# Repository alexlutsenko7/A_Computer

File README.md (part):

# L

**Supported hardware (since 2026-11-23): the QMTECH Cyclone 10 LP core board (10CL025) with I/O board revision 2
and the firmware `ESP32/v2`.** The first set, the Cyclone IV EP4CE15 core board with I/O board revision 1 and the
firmware `ESP32/v1`, is **no longer supported**: its FPGA and the ESP32 module without extra memory are too small
for the newer machines and functions. Everything for it stays in this repository as it was last built and tested
(sources, `ep4_ce15/` projects, `ESP32/v1`, the files in `INSTALL/`), because the book describes it; it gets no
new functions and is not built or tested any more. The `<machine>/ep4_ce15/` folders also hold the sources that the
10CL025 projects use, so they go on changing; a change there is tried on the 10CL025 only.

Retro computers in an FPGA: an Intel/Altera Cyclone IV E (EP4CE15F23C8) on a QMTECH core board, with the RAM and
ROMs in the board's SDRAM, VGA output, a USB keyboard and an ESP32 system controller (SD card loader, on-screen
menus, Bluetooth audio). A machine menu at power-up chooses the machine:

- **LSpectrum**, a ZX Spectrum 128K with a built-in SD card tape loader that plays unmodified `.tap` / `.tzx` files,
  saves programs back to the card, and saves / loads `.z80` snapshots;
- **L64**, a Commodore 64 (PAL) with a 1541 disk drive that reads and writes `.d64` images, `.prg` / `.t64`
  loading, C64 `.tap` tapes, turbo loading and `.a64` snapshots;
- **LTari**, an Atari 800XL (**LTari 800**, 64 KB) or 130XE (**LTari 130**, 128 KB) with its own ANTIC, GTIA, POKEY
  and PIA, an SD card disk drive (`.atr`), `.xex` / `.com` programs, cartridges (`.car`) and `.a8s` snapshots.

Status (October 2026): the menu, LSpectrum, L64 and LTari work on hardware.

**Licences, what is our own work, and the complete build guide (including the C64 ROM files you have to get
yourself): [BUILDING_AND_LICENSES.md](BUILDING_AND_LICENSES.md).**

## Features

- **ZX Spectrum 128K**: T80 Z80 core at the exact 3.5469 MHz, or 28 MHz turbo; 128 KB RAM with 7FFD paging; 128K
  ROM set and DiagROM; AY-3-8912 (JT49); beeper; Kempston joystick; 50 Hz interrupt; memory contention (128K
  timing, memory and I/O cycles; not cycle-exact) and the floating bus, so most timing-critical games and border
  effects run as on the real machine.
- **Memory in SDRAM**: own 112 MHz controller for the W9825G6KH (open-row, CAS latency 2); the CPU is stepped by a
  clock enable and simply waits when the SDRAM is busy. The screen is mirrored in block RAM for the video.
- **Video**: VGA 720x576@50 (576p) or 640x480@60, 2 bits per colour, switchable at run time.
- **USB keyboard** through a CH9350-style UART module, with machine keys: DiagROM, 50/60 Hz, reset.
- **SD card tape loader** on an ESP32 system controller (firmware in C, SPI link to the FPGA):
  - on-screen browser (folders, long names, up to 320 entries), FAT16 / FAT32;
  - plays TAP and TZX (incl. turbo blocks, pure tones, pulse sequences, direct recordings, loops, jumps, calls,
    stop blocks) T-state exact, in turbo (8x) or at normal speed;
  - saves: everything the Spectrum `SAVE`s goes into a `.tap` file on the card;
  - pause, back one block, stop;
  - **snapshots**: F2 saves the whole machine as a `.z80` (version 3, 128K) at any moment; the browser loads
    `.z80` files (versions 1-3, 48K and 128K).
- **Bluetooth audio**: the same ESP32-WROOM-32 (`ESP32/v2/`, Arduino) takes the sound as I2S and sends it to Bluetooth
  speakers / headphones (A2DP), including old PIN-only devices; F3 opens the on-screen Bluetooth menu.
- **L64** (`L64/ep4_ce15/README.md`): VIC-II Kawari, T65 as 6510, the MiSTer SID 6581/8580 and CIAs, our bus, PLA
  and 1541 drive (T65, two VIAs, GCR on the fly from a track buffer the ESP32 fills from the `.d64`). The
  picture goes through a frame buffer in SDRAM: 800x600 at 60 Hz, or the C64's own 50 Hz (F8). Turbo loading (F6):
  CPU, CIAs and 1541 up to 4x while a motor runs. F2 snapshots (`.a64`). The C64 ROMs are not part of the project:
  the ESP32 installs your own ROM files from the SD card into the flash.
- **LNES** (`LNES/ep4_ce15/README.md`, both core boards; **new, tested in simulation only**): the Nintendo Entertainment System
  (NTSC). Own picture processor, sound and cartridge logic (mappers 0, 1, 2, 3, 4, 7, 11, 66) written from the NESdev
  documentation, T65 as the 2A03's processor. Games (`.nes`) load from the SD card; battery RAM is kept as a `.SAV` file.
  The joystick gives the directions and one button, the other pad buttons are keys.
- **LMega** (`LMega/10cl025/README.md`, Cyclone 10 LP 10CL025 board only; **new, tested in simulation only**): the Sega Mega
  Drive / Genesis from open cores (fx68k, jt12, jt89, the MiSTer Genesis video processor, T80) with our memory, video
  output (line doubler) and bus. Games (`.md`, `.gen`, `.bin`, `.smd`, up to 4 MB) load from the SD card. F8 steps through
  the video modes of a game made for 50 Hz.
- **LNext** (`LNext/10cl025/README.md`, Cyclone 10 LP 10CL025 board only): the ZX Spectrum Next. The open Spectrum Next core in its MiSTer port (`ZXNEXT/`, unchanged) with our
  memories for this FPGA, SDRAM controller, video output (line doubler) and keyboard. It starts from the SD card as a
  real Next does: the card must hold the Spectrum Next distribution (`TBBLUE.FW`, `machines`, `nextzxos` ...; not part
  of this project). The card is on the ESP32, which moves its sectors to an SD card made of logic inside the FPGA.
  The ESP32 also plays tape files (F12) into the Next's tape input for the 48K / 128K machines and, with I/O board
  revision 2, is the Next's Wi-Fi module (it answers the ESP8266 AT commands; Bluetooth audio keeps playing).
- **Machine menu** (`AMenu/ep4_ce15/`): the factory image at flash 0 starts a machine through the Cyclone IV remote update
  block; KEY1 in a machine returns to it.
- **Fully constrained timing**: every clock and I/O constrained, timing met at all corners.

## Hardware

| Part | Notes |
|---|---|
| QMTECH Cyclone IV core board | EP4CE15F23C8N, 50 MHz oscillator, W9825G6KH-6 SDRAM (32 MB), W25Q64 configuration flash |
| I/O board (own design, `Extra_PCB_CycloneIV/`) | 4-bit-per-colour VGA DAC, two Kempston DB9, 3.5 mm audio jack (AY + beeper, line level), USB keyboard module (UART, 3.3 V), microSD socket, sockets for the ESP32; wired to the core board's U8 |
| I/O board revision 2 (own design, `Extra_PCB_CycloneIV_R2/`, ordered 2026-11-03) | as revision 1, with everything on the board: ESP32-WROVER-E module, CP2102N USB-C console / 5 V input, CH9350L with a USB-A keyboard socket, a second USB-A (5 V for a VGA2HDMI dongle); 4 layers; same J1 to the core board's U8 |
| Pad board (own design, `Extra_PCB_Pads_U7/`, designed and ordered 2026-11-23, not built yet) | on the 10CL025 core board's second header (U7): two DB9 sockets for Sega Mega Drive pads (3 and 6 buttons) on 5 V, level shifters to the FPGA pins (74LVC245, 74HCT2G34), 84.1 x 19.5 mm; no FPGA logic for it yet |
| ESP32-WROOM-32 dev board | system controller on the I/O board: SD card, tape loader, Bluetooth audio (`ESP32/v2/README.md`) |

Pin assignments: `docs/BOARD_PINOUT.md`.

## Repository layout

AMenu, LSpectrum, L64, LTari and DDR_TEST each hold one subfolder per core board: `ep4_ce15/` (QMTECH Cyclone IV EP4CE15: all sources, simulations and tools) and `10cl025/` (QMTECH Cyclone 10 LP 10CL025YU256: the Quartus project only, generated by `tools/mk_10cl025_qsf.py`; it uses the sources of `ep4_ce15/`). The 10CL025 builds meet timing but have **not been tried on hardware** yet. An `L.jic` or `LUPDATE.BIN` is for one board only: `AMenu/<board>/output_files/`.

| Folder | Contents |
|---|---|
| `AMenu/ep4_ce15/` | machine menu shown at power-up (factory image); `L.cof` -> `output_files/L.jic`, the ready-to-program image with all machines |
| `LSpectrum/ep4_ce15/` | **The Spectrum**: Quartus project, `rtl/` (Verilog), `sim/` (Questa testbenches) |
| `ESP32/` | **the ESP32 firmware**, the same for all machines and both FPGA boards (loader + Bluetooth): `v1/` for I/O board revision 1 (in use), `v2/` for revision 2; each an Arduino sketch (`v1.ino` / `v2.ino`) with its sources in `src/` |
| `ESP32_test/` | tests of the firmware: `v1/`, `v2/` with the PC tests (`test/`) and their tools (`tools/`); `v1/` also holds the hardware test sketches `ESPLinkTest/` (SPI link) and `Test_wires/` (ESP32 <-> FPGA wiring) |
| `L64/ep4_ce15/` | **The Commodore 64**: Quartus project, `rtl/` (our bus, 1541, video; Kawari VIC-II, SID, CIA, VIA), `sim/`, `tools/` (ROM image, test disk) |
| `LNES/ep4_ce15/` | **The NES**: Quartus project, `rtl/` (own PPU, APU, mappers, frame buffer), `sim/`, `tools/` (sound tables, palette); `LNES/10cl025/` the project for the other board |
| `LMega/10cl025/` | **The Sega Mega Drive** (10CL025 only): Quartus project, `rtl/` (our bus, memory, video; `rtl/genesis/` the MiSTer video processor, unchanged), `sim/` |
| `FX68K/`, `JT12/`, `JT89/` | 68000, YM2612 and SN76489 cores, from the MiSTer Genesis core, unchanged (`SOURCE.md` in each) |
| `LNext/10cl025/` | **The ZX Spectrum Next** (10CL025 only): Quartus project, `rtl/` (our memories, SDRAM, SD card link, keyboard, video), `sim/`, `tools/` |
| `ZXNEXT/` | the Spectrum Next core (MiSTer port) and the MiSTer SD card of logic, unchanged (`ZXNEXT/SOURCE.md`) |
| `T65/` | 6502 core (VHDL), from the MiSTer C64 core, unchanged (`T65/SOURCE.md`) |
| `tests/` | FPGA test projects: `Test_wires/fpga/` (ESP32 <-> FPGA wiring, FPGA side; the sketch is `ESP32_test/v1/Test_wires/`), `t80_fmax/`, `jtag_rig/` (testing a core board without its I/O board: keys, status and the video picture over JTAG) |
| `T80/` | Z80 core (VHDL), from the MiSTer ZX Spectrum core, unchanged (`T80/SOURCE.md`) |
| `DDR_TEST/` | stand-alone SDRAM controller + memory test (the controller used by LSpectrum): `ep4_ce15/` for the Cyclone IV EP4CE15 core board, `10cl025/` the same test for the QMTECH Cyclone 10 LP 10CL025 core board |
| `VGA_TEST/` | stand-alone VGA test (colour bars, both video modes) |
| `Extra_PCB_CycloneIV/` | **the I/O board, revision 1**: KiCad 10 project (schematic + PDF, routed 2-layer layout, project symbols / footprints), JLCPCB order files (`jlcpcb/`: Gerbers, drill, BOM, CPL), wiring to the core board (`README.md`) |
| `Extra_PCB_CycloneIV_R2/` | **the I/O board, revision 2**: KiCad 10 project (schematic + PDF, routed 4-layer layout with GND / +3V3 planes, project footprints incl. the ESP32-WROVER-E), JLCPCB order files (`jlcpcb/`), generator / routing scripts (`tools/`), `README.md` |
| `3D_case/` | **printed case** for the 10CL025 core board on the I/O board revision 2: two halves (bottom with pins through the I/O board's holes, top glued on), `case.py` (CadQuery) and the STL / STEP files in `out/`, `README.md` |
| `docs/` | design notes, user documents, data sheets (see below) |

## Building

Step by step, from the tools to the SD card: [BUILDING_AND_LICENSES.md](BUILDING_AND_LICENSES.md), section 4.
Tools: Quartus Prime 25.1std Lite (Windows) for the FPGA; Arduino (core esp32 3.3.2, `arduino-cli`) for the ESP32
(libraries: `ESP32/v2/README.md`). The scripts are written for WSL on Windows and call the Windows tools;
paths are at the top of each script.

```
cd LSpectrum/ep4_ce15
quartus_sh --flow compile LSpectrum              # -> output_files/LSpectrum.sof
cd ../L64
quartus_sh --flow compile L64                # -> output_files/L64.sof
cd ../AMenu
quartus_sh --flow compile AMenu                  # machine menu
quartus_cpf -c L.cof                      # -> output_files/L.jic (menu + machines + ROMs)
cd ../..
arduino-cli compile -b esp32:esp32:esp32 -u -p COM10 ESP32/v1    # ESP32 firmware (loader + Bluetooth), I/O board revision 1
```

Flash layout: the menu at 0, then three machines of 2 MB each (bitstream at 0x100000 / 0x300000 / 0x500000, the
machine's ROM area 1 MB above it). `L.jic` holds LSpectrum, L64 and LTari 800; every machine, LTari 130 too, is also a
machine file that the menu installs from the SD card's `MACHINES` folder into any of the three positions (F12). The C64
ROMs are written by the ESP32 into L64's ROM area; ROMs are copied into SDRAM at every reset.
A change in `ESP32/v2/` needs only the ESP32 flashed again; a change in `LSpectrum/ep4_ce15/rtl/` a new compile.

## Programming

Quartus Programmer, JTAG, add `AMenu/ep4_ce15/output_files/L.jic`, tick Program/Configure, program, then
power-cycle the board. After that, `.sof` loads over JTAG are enough during development (the ROMs stay in the flash).

## Using it

The keys below are LSpectrum's; L64's (mostly the same F keys) are in `docs/L64_Keys.docx` and `L64/ep4_ce15/README.md`.

| Key | Function |
|---|---|
| F12 | tape browser (Enter plays a tape / loads a `.z80` snapshot; first line *[Save to this folder]* starts saving) |
| F2 | save a snapshot: type a name, Enter (`NAME.Z80` in the browser's current folder) |
| F12 while saving | stop saving and close the file |
| Keypad 5 / F11 | pause / continue the tape |
| Keypad - | back one block |
| F7 | stop the tape |
| F5 | memory contention and floating bus on (default) / off |
| F6 | tape speed: turbo (default) / normal |
| F8 | 60 / 50 Hz video (starts at 640x480@60; border effects line up only at 50 Hz) |
| Page Up / Page Down | browser open: page through the list; closed: move the 50 Hz frame interrupt 1/8 line to line up border effects (default 24.1, set for Aquaplane) |
| F1 held at start | the diagnostics ROM slot instead of the 128K ROM (the public image has 48K BASIC there; add DiagROM yourself with `LSpectrum/ep4_ce15/tools/mk_roms48k.py`) |
| KEY0 (board) | reset everything |
| Ctrl+Alt+Del, KEY1 (board) | back to the machine menu (Ctrl+Alt+Del when released) |

Loading: `LOAD ""` (or *Tape Loader* in the 128K menu), F12, choose the file, Enter.
Saving: F12, *[Save to this folder]*, type a name, Enter, then `SAVE` on the Spectrum as often as you like; F12 ends.
Snapshot: F2 at any moment, type a name, Enter; load it later from the F12 browser.
SD card: FAT32 or FAT16 (not exFAT).

At power-up the machine menu (`AMenu/ep4_ce15/`) appears: Up/Down + Enter, the digit, or a joystick starts a machine.

The complete key list with step-by-step usage is in `docs/LSpectrum_Keys.docx`.

## Testing

```
bash ESP32_test/v2/test/run_host_test.sh       # PC: FAT reading/writing, every TAP/TZX signal vs a Python reference, saving, .z80
bash LSpectrum/ep4_ce15/sim/run_esp_link_sim.sh           # RTL: loader hardware driven over the SPI link by an ESP32 model
bash LSpectrum/ep4_ce15/sim/run_sim.sh                    # RTL: whole machine boots the 128K ROM
bash LSpectrum/ep4_ce15/sim/run_snap_sim.sh               # RTL: snapshot freeze / restore with the real T80
bash LSpectrum/ep4_ce15/sim/run_cont_sim.sh               # RTL: memory contention (NOPs per line in contended RAM: 57 / 41)
bash LSpectrum/ep4_ce15/sim/run_float_sim.sh              # RTL: floating bus (IN A,(FF) against Fuse's 128K rule)
bash LSpectrum/ep4_ce15/sim/run_floatgame_sim.sh          # RTL: a .z80 game's floating-bus sync vs Fuse (default Sidewize)
bash AMenu/ep4_ce15/sim/run_sim.sh                        # RTL: machine menu with a model of the remote update block
bash L64/ep4_ce15/sim/run_sim.sh ROMIMAGE.mem         # RTL: whole C64 boots to READY (your own ROM image); +define+DISK: 1541 directory
bash L64/ep4_ce15/sim/run_gcr_sim.sh                  # RTL: 1541 GCR encoder / decoder
```

The PC tests need a Windows gcc (w64devkit); the simulations need Questa (Intel FPGA Starter Edition).

## Documentation

| Document | Contents |
|---|---|
| `docs/LSpectrum_Architecture.docx` | architecture of the whole machine: block diagram, clocks, memory, video, tape loader, pins, timing |
| `docs/LSpectrum_Keys.docx` | all keys and usage cases |
| `docs/LSpectrum_FKeys.docx` | short sheet of the F keys |
| `docs/L_Build_and_Install.docx` | step by step: building the three FPGA images, the one .jic, programming, the ESP32, the SD card and its ROM files, how the ROMs are used |
| `docs/L64_Keys.docx` | the machine menu and L64: all keys, the C64 keyboard layout, usage cases (ROMs, disk, tape, snapshots, 60 / 50 Hz) |
| `docs/SD_TAPE_LOADER.md` | SD tape loader: design, registers, firmware, saving, snapshots |
| `docs/SDRAM_CONTROLLER.md`, `docs/SDRAM_TUTORIAL.md` | the SDRAM controller in detail, and an SDRAM tutorial |
| `docs/T80_CEN_ANALYSIS.md` | running the T80 from a clock enable at 112 MHz |
| `docs/BOARD_PINOUT.md` | core board headers and the I/O board wiring |
| `docs/KNOWN_ISSUES.md` | open issues and limitations |
| `docs/L_User_Manual.docx` | user manual: connecting, the machine menu, choosing the machines, the SD card, keys of every machine; in nine languages in `docs/manuals/doc/` |
| `docs/L_Third_Party.docx` | every external core and library: origin, licence, how much of it is used |
| `docs/PLAN.md` | design decisions and development log |

## Licences

The project's own files are under the MIT licence (`LICENSE`). Third-party parts keep their own licences:

| Part | Licence |
|---|---|
| `T80/` (Z80 core, Daniel Wallner; Sorgelig) | BSD-style, see the file headers |
| `T65/` (6502 core, Daniel Wallner et al.) | BSD-style, see the file headers |
| `LSpectrum/ep4_ce15/rtl/jt49/` (AY-3-8910 core, Jose Tejada) | **GPL-3**: a bitstream that includes it is a GPL-3 work |
| `L64/ep4_ce15/rtl/vicii/` (VIC-II Kawari, Randy Rossi) | **GPL-3** |
| `L64/ep4_ce15/rtl/via/` (VIA 6522, Gideon Zweijtzer) | **GPL-3** |
| `L64/ep4_ce15/rtl/sid/`, `L64/ep4_ce15/rtl/cia/` (MiSTer C64 core) | CERN-OHL-S v2 (`sid_dac.sv`, `sid_filter.sv`) and GPL (the MiSTer C64 core) |
| `FX68K/` (68000, Jorge Cwik), `JT12/`, `JT89/` (YM2612, SN76489, Jose Tejada) | **GPL-3** |
| `LMega/10cl025/rtl/genesis/` (Mega Drive video processor: Gregory Estrade, Till Harbaum, Alexey Melnikov, György Szombathelyi) | BSD-style, see the file headers and `SOURCE.md` |
| `ZXNEXT/rtl/` (ZX Spectrum Next core: Alvin Albrecht, Victor Trucco, Fabio Belavenuto; MiSTer port Alexey Melnikov), `LNext/10cl025/rtl/next_sdram.v` (after the port's SDRAM controller) | **GPL-3** (the controller: GPL-2 or later) |
| `ZXNEXT/sys/sd_card.sv` (Till Harbaum, Sorgelig) | LGPL-3 |
| Spectrum Next firmware, ROMs and NextZXOS (`TBBLUE.FW`, `machines/`, `nextzxos/`) | **not included**: get the distribution from specnext.com and copy it to the SD card |
| `ESP32/v2/` uses ESP32-A2DP (Phil Schatzmann) | Apache-2.0 (library, not included) |
| ROM images in `LSpectrum/ep4_ce15/roms48k.hex` and `LSpectrum/ep4_ce15/sim/roms.mem` | ZX Spectrum 128 ROMs (c) Amstrad, distributed for emulator use with permission, copyright messages unchanged. Retroleum's DiagROM is not included (its licence is not known): the published image has a copy of the 48K BASIC ROM in that slot; `LSpectrum/ep4_ce15/tools/mk_roms48k.py` builds the image with your own copy |
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
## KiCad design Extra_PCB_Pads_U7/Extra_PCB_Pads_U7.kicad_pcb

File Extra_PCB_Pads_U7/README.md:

# Extra_PCB_Pads_U7 — pad board for the 10CL025 core board's header U7

KiCad 10 project. Two DB9 sockets for **Sega Mega Drive pads** (3 and 6 buttons) on 5 V, with level shifters to
the FPGA's 3.3 V pins. Atari-style joysticks and Master System pads work in the same sockets.

Status (2026-11-23): designed, routed, rules check clean. **Bare boards and parts ordered separately (user, 2026-11-23); the user assembles them by hand.** Not built yet, no FPGA logic for it yet.

## Size and mounting

- **84.1 x 19.5 mm**, 2 layers, no mounting holes. As long as the core board and flush with it on both sides.
- It lies under the core board's U7 edge the way the I/O board lies under the U8 edge: the two header rows are
  soldered through both boards, the core board covers the last 6.04 mm of this board, 3 mm above it.
- Top side (the side facing the core board): the two DB9 sockets, openings away from the core board.
- Bottom side: all other parts.
- The height is set by the DB9 socket (CONNFLY DS1037-09M, as on the I/O board): 12.9 mm of socket, 0.6 mm gap
  to the core board's edge, 6.04 mm under the core board.

## Circuit

| Part | Does |
|---|---|
| J1 | 2x32 holes = U7, pin for pin (no pair swap) |
| J2, J3 | DB9 sockets, pad 1 and pad 2 |
| U1, U2 (74LVC245 on 3.3 V) | six lines per socket from the pad to the FPGA; the inputs tolerate 5 V |
| U3 (74HCT2G34 on 5 V, dual buffer in SOT-23-6) | both select lines from the FPGA to the pads; reads a 3.3 V high as high |
| R1-R6, R9-R14 (3k3 to 5 V) | pull-ups on the socket lines (a joystick only shorts them to ground) |
| R7, R15 (10k to 3.3 V) | select is high while the FPGA pin is not driven |
| R8, R16 (100 Ohm) | in series with the select pin of the socket |
| C1-C6 | decoupling, 10 uF on the 5 V input |

DB9 pin 5 is connected straight to the 5 V (no fuse, user's choice): a short in a pad or its cable loads the
board's 5 V input directly, as the I/O board's USB sockets do.

DB9 pins: 1 Up, 2 Down, 3 Left, 4 Right, 5 supply 5 V, 6 B (A with select low), 7 select, 8 ground,
9 C (Start with select low).

## Header pins and FPGA balls

The balls are read from the QMTECH 10CL025 schematic V1. **Check the header with a meter before soldering**: pins 1 / 2
and 61 / 62 ground, 3 / 4 3.3 V, 63 / 64 5 V; the silkscreen marks pin 1 and pin 63.

| Signal | U7 pin | FPGA ball | Direction |
|---|---|---|---|
| PAD1_UP | 21 | D6 | pad -> FPGA |
| PAD1_DOWN | 23 | B5 | pad -> FPGA |
| PAD1_LEFT | 26 | B6 | pad -> FPGA |
| PAD1_RIGHT | 27 | A6 | pad -> FPGA |
| PAD1_B | 30 | A7 | pad -> FPGA |
| PAD1_C | 31 | D8 | pad -> FPGA |
| PAD1_SEL | 32 | C8 | FPGA -> pad |
| PAD2_SEL | 33 | C9 | FPGA -> pad |
| PAD2_UP | 34 | D9 | pad -> FPGA |
| PAD2_DOWN | 35 | F9 | pad -> FPGA |
| PAD2_LEFT | 36 | E9 | pad -> FPGA |
| PAD2_RIGHT | 37 | E10 | pad -> FPGA |
| PAD2_B | 38 | E11 | pad -> FPGA |
| PAD2_C | 44 | B10 | pad -> FPGA |

Not used on purpose: pin 7 (G1, the machines' menu key input), the configuration pins (17, 20, 22, 24, 25, 28, 29),
the clock inputs (39-42). Pins 5 / 6 and 47-60 are not connected.

All lines are low when a button is pressed. The 5 V comes from the core board's input (U7 63 / 64), so from the
I/O board's USB-C socket.

## Open points

- The header's row order (even pins on the row nearer the core board's edge) is read from the photo in QMTECH's
  manual. If it is the other way round, every signal sits on its pair's partner pin: a change of the FPGA pin
  list, not of the board; the supply pairs carry the same net on both pins.
- Part numbers for an assembly order are not checked (74LVC245 in TSSOP-20, 74HCT2G34GV in SOT-457 on the SOT-23-6
  footprint); Gerbers in `jlcpcb/` (no parts list or placement file: hand assembly).
- The printed case has no openings on this side.
- Rules check: no errors; left are three ground pads with one thermal spoke (they also have a track) and one
  silkscreen note.

## Files and tools

| File | What |
|---|---|
| `Extra_PCB_Pads_U7.kicad_sch` / `.pdf` | schematic (generated; every pin carries a net label) |
| `Extra_PCB_Pads_U7.kicad_pcb` | board |
| `out/top.png`, `out/bottom.png` | pictures of both sides |
| `tools/design.py` | parts and nets, the single source |
| `tools/gen_sch.py`, `tools/mk_pro.py` | schematic and project file (WSL python, run in this folder) |
| `tools/placement.py`, `tools/mk_pcb.py build` | positions, board from the netlist (KiCad python) |
| `tools/route.py dsn / import / pour` | FreeRouting 2.5.0 in between (`-de pads.dsn -do pads.ses -mp 40`) |
| `tools/finish.py` | tracks off the board edge, silkscreen |

Once the board is edited in KiCad, the KiCad files are the source of truth: do not rebuild over them.

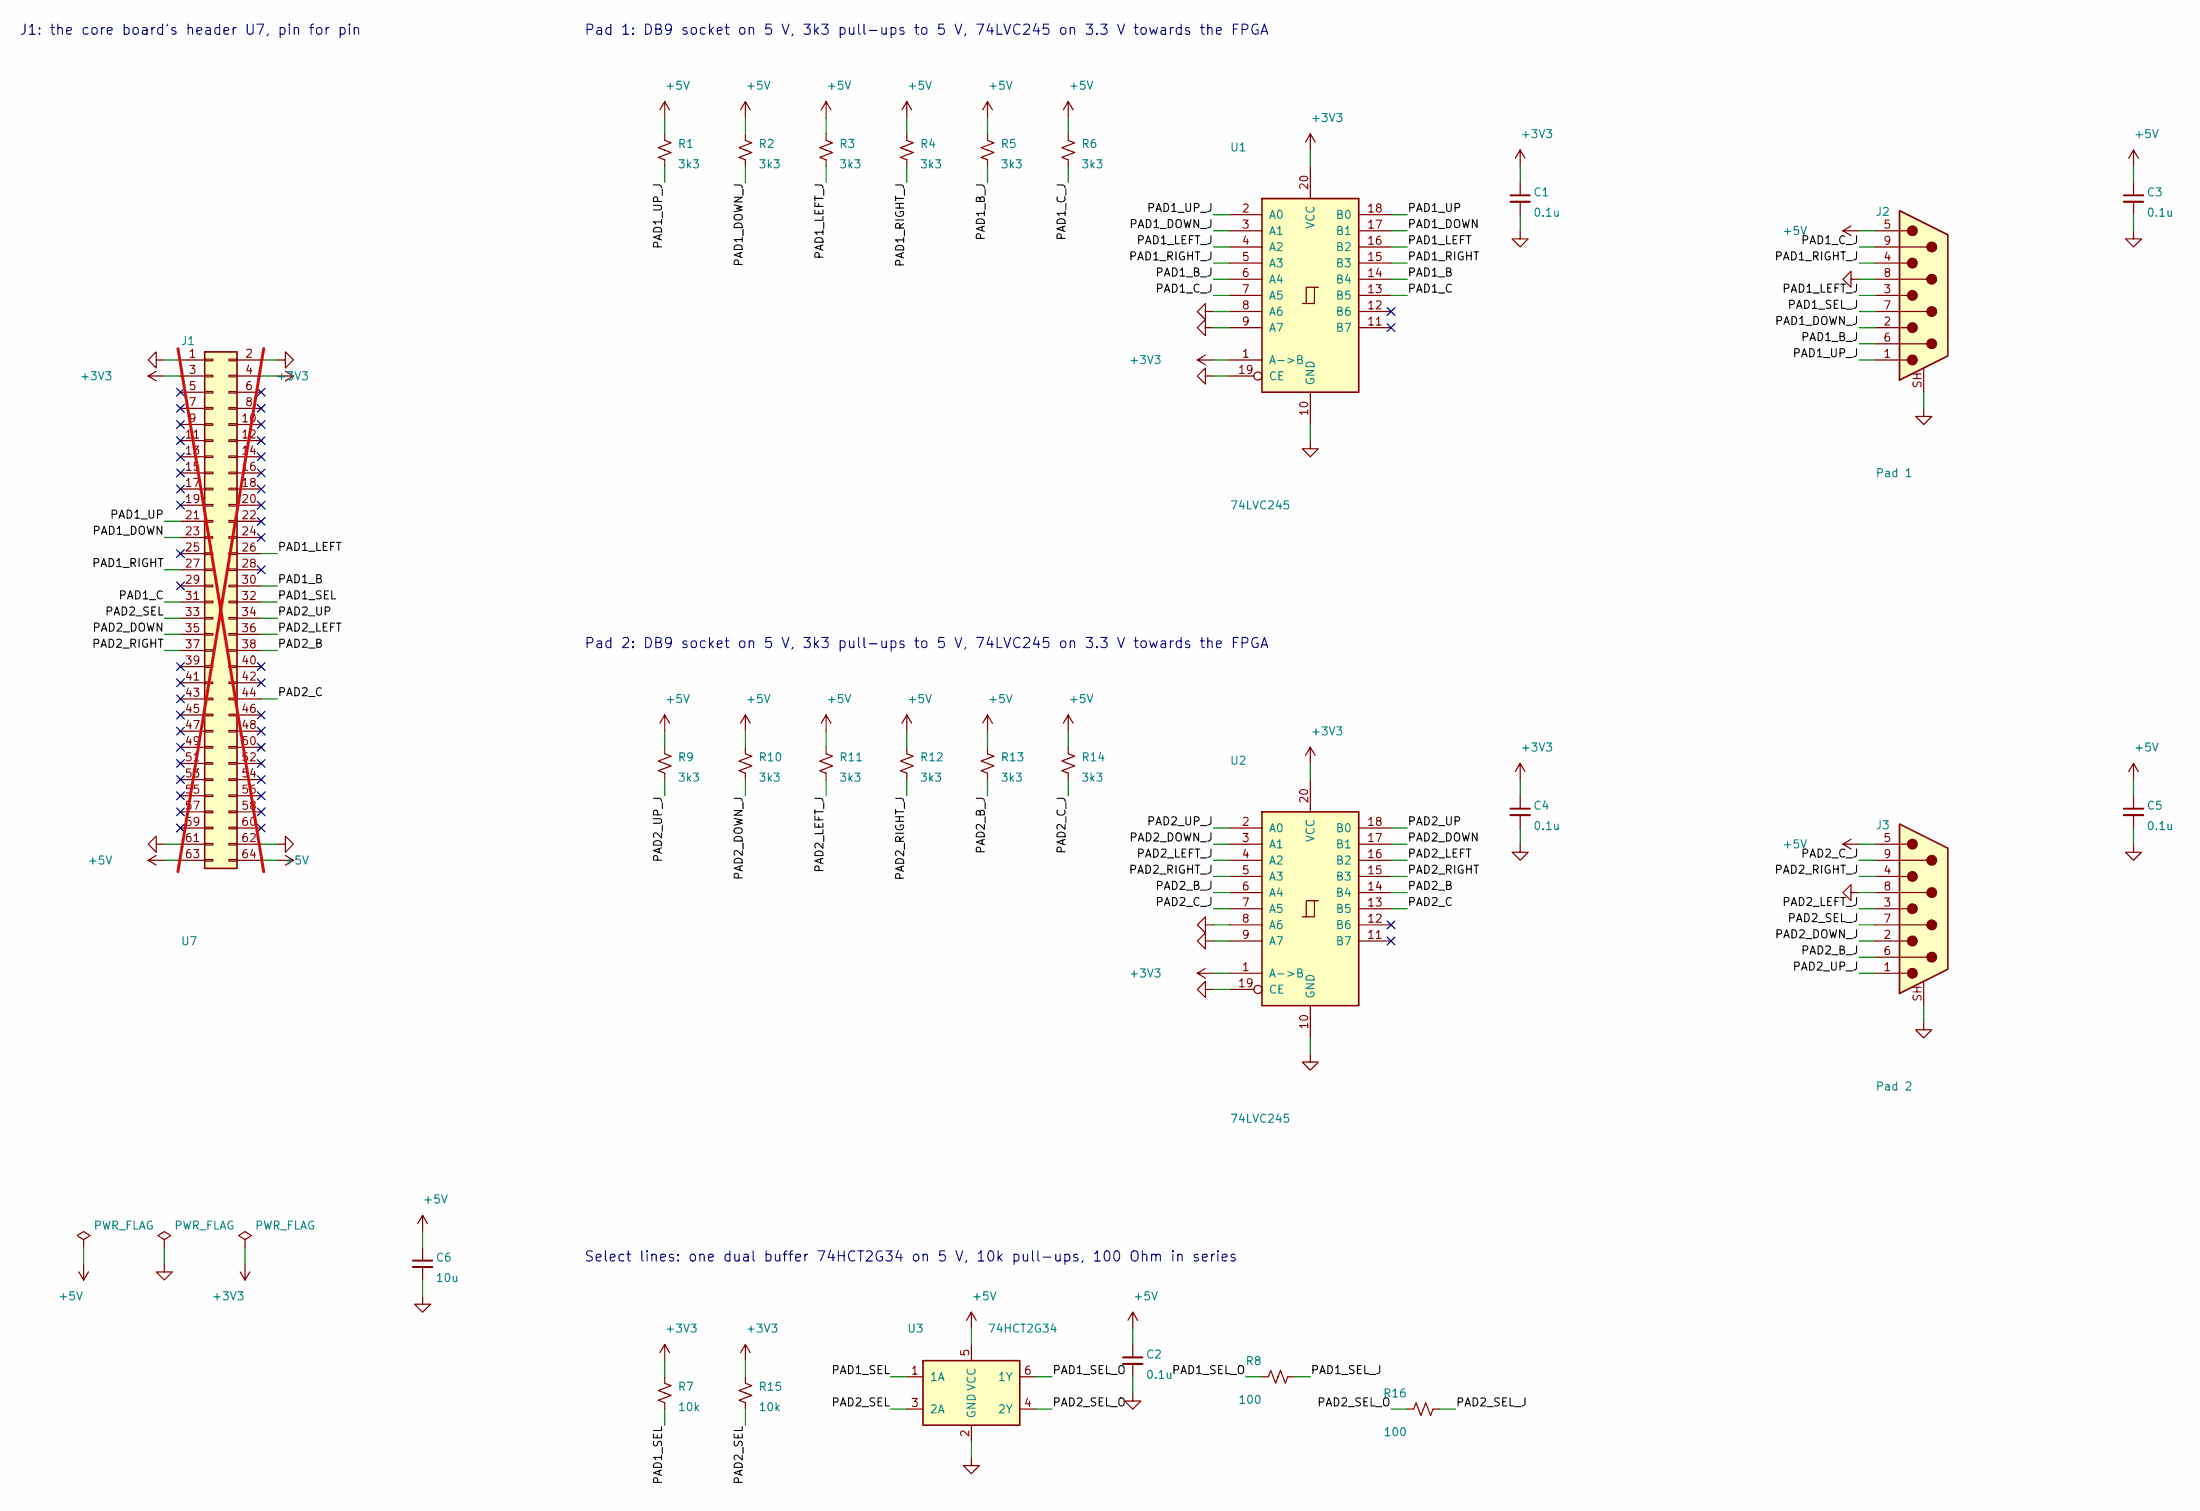
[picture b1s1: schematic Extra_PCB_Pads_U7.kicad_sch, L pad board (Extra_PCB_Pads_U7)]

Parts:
C1, C2, C3, C4, C5: 0.1u; C_0603_1608Metric
C6: 10u; C_0805_2012Metric
J1: U7; PinHeader_2x32_P2.54mm_Vertical; not fitted
J2: Pad 1; DSUB-9_Pins_Horizontal_P2.77x2.84mm_EdgePinOffset7.70mm_Hou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; MPN DS1037-09MNAKT74-0CC
J3: Pad 2; DSUB-9_Pins_Horizontal_P2.77x2.84mm_EdgePinOffset7.70mm_Hou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; MPN DS1037-09MNAKT74-0CC
R1, R2, R3, R4, R5, R6, R9, R10, R11, R12, R13, R14: 3k3; R_0603_1608Metric
R7, R15: 10k; R_0603_1608Metric
R8, R16: 100; R_0603_1608Metric
U1, U2: 74LVC245; TSSOP-20_4.4x6.5mm_P0.65mm; MPN SN74LVC245APWR
U3: 74HCT2G34; SOT-23-6; MPN 74HCT2G34GV

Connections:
+3V3: C1.1, C4.1, J1.3, J1.4, R7.1, R15.1, U1.1 (A->B), U1.20 (VCC), U2.1 (A->B), U2.20 (VCC)
+5V: C2.1, C3.1, C5.1, C6.1, J1.63, J1.64, J2.5, J3.5, R1.1, R2.1, R3.1, R4.1, R5.1, R6.1, R9.1, R10.1, R11.1, R12.1, R13.1, R14.1, U3.5 (VCC)
/PAD1_B: J1.30, U1.14 (B4)
/PAD1_B_J: J2.6, R5.2, U1.6 (A4)
/PAD1_C: J1.31, U1.13 (B5)
/PAD1_C_J: J2.9, R6.2, U1.7 (A5)
/PAD1_DOWN: J1.23, U1.17 (B1)
/PAD1_DOWN_J: J2.2, R2.2, U1.3 (A1)
/PAD1_LEFT: J1.26, U1.16 (B2)
/PAD1_LEFT_J: J2.3, R3.2, U1.4 (A2)
/PAD1_RIGHT: J1.27, U1.15 (B3)
/PAD1_RIGHT_J: J2.4, R4.2, U1.5 (A3)
/PAD1_SEL: J1.32, R7.2, U3.1 (1A)
/PAD1_SEL_J: J2.7, R8.2
/PAD1_SEL_O: R8.1, U3.6 (1Y)
/PAD1_UP: J1.21, U1.18 (B0)
/PAD1_UP_J: J2.1, R1.2, U1.2 (A0)
/PAD2_B: J1.38, U2.14 (B4)
/PAD2_B_J: J3.6, R13.2, U2.6 (A4)
/PAD2_C: J1.44, U2.13 (B5)
/PAD2_C_J: J3.9, R14.2, U2.7 (A5)
/PAD2_DOWN: J1.35, U2.17 (B1)
/PAD2_DOWN_J: J3.2, R10.2, U2.3 (A1)
/PAD2_LEFT: J1.36, U2.16 (B2)
/PAD2_LEFT_J: J3.3, R11.2, U2.4 (A2)
/PAD2_RIGHT: J1.37, U2.15 (B3)
/PAD2_RIGHT_J: J3.4, R12.2, U2.5 (A3)
/PAD2_SEL: J1.33, R15.2, U3.3 (2A)
/PAD2_SEL_J: J3.7, R16.2
/PAD2_SEL_O: R16.1, U3.4 (2Y)
/PAD2_UP: J1.34, U2.18 (B0)
/PAD2_UP_J: J3.1, R9.2, U2.2 (A0)
GND: C1.2, C2.2, C3.2, C4.2, C5.2, C6.2, J1.1, J1.2, J1.61, J1.62, J2.8, J2.SH (PAD), J3.8, J3.SH (PAD), U1.8 (A6), U1.9 (A7), U1.10 (GND), U1.19 (CE), U2.8 (A6), U2.9 (A7), U2.10 (GND), U2.19 (CE), U3.2 (GND)

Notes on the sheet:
J1: the core board's header U7, pin for pin
Pad 1: DB9 socket on 5 V, 3k3 pull-ups to 5 V, 74LVC245 on 3.3 V towards the FPGA
Pad 2: DB9 socket on 5 V, 3k3 pull-ups to 5 V, 74LVC245 on 3.3 V towards the FPGA
Select lines: one dual buffer 74HCT2G34 on 5 V, 10k pull-ups, 100 Ohm in series

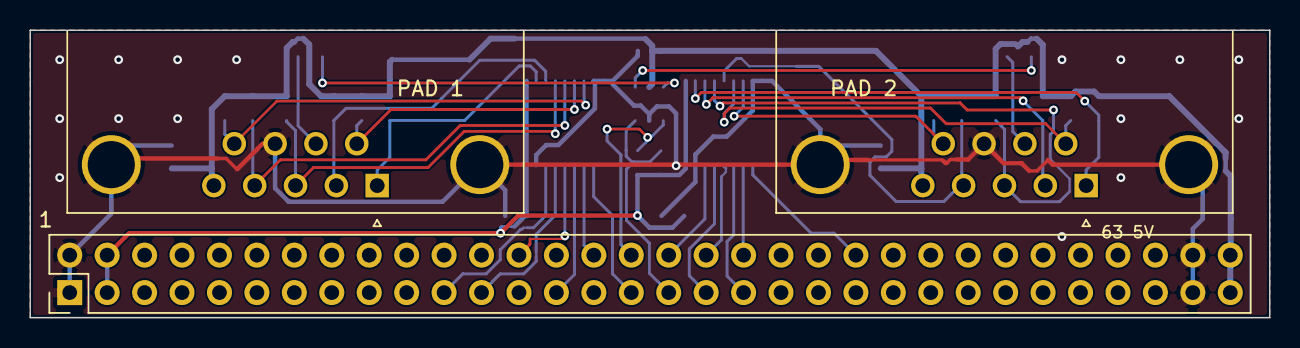
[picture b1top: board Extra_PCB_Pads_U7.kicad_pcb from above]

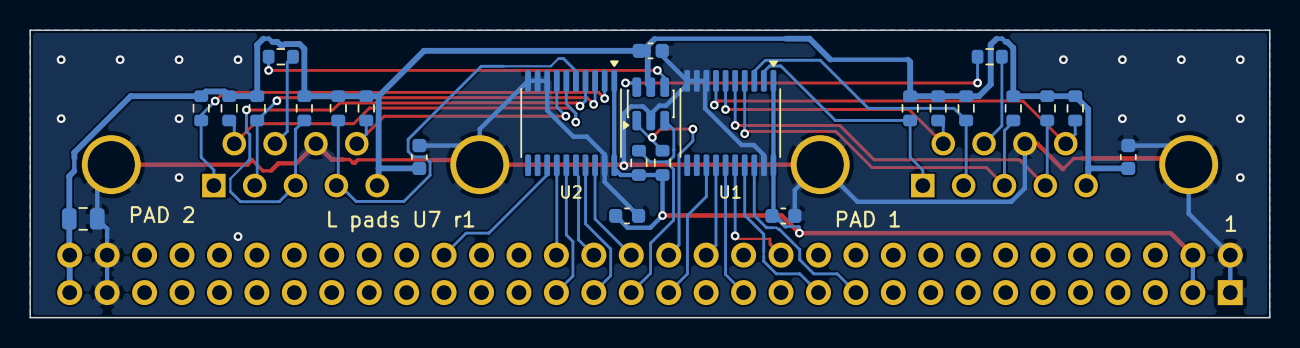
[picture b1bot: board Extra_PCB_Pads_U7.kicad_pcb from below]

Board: 2 copper layers, 84.1 x 19.5 mm, 28 parts (25 on the bottom side), 33 nets.

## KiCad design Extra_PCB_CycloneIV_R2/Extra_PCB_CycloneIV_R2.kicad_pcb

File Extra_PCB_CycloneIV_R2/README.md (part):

# Extra_PCB_CycloneIV_R2 — I/O board, revision 2

KiCad 10 project for the second revision of the L I/O board (revision 1 = `../Extra_PCB_CycloneIV/`, as built).
The board sits beside the QMTECH Cyclone IV core board and is wired to its U8 through J1, exactly as revision 1
(same J1 pinout, same pair-swapped wiring), so the FPGA images do not change. The ESP32 firmware is
`ESP32/v2` (control UART on other pins, PSRAM build).

J1 also fits the **QMTECH Cyclone 10 LP 10CL025 core board** (10CL025YU256, schematic V1 2023-11-09). The board is the
same size (84.1 x 67.1 mm), and its U8 sits at the same place and the same way round: pin 1 at the left end of the outer
row, VIN at the right end. Its U8 power pins match (1/2 GND, 3/4 3V3, 61/62 GND, 63/64 VIN), except that pins **5/6 are
GND** on the 10CL025 (clock inputs on the EP4CE15). J1 leaves 5/6 unconnected, and they must stay that way. U8 pins 7-60
are all 3.3 V I/O on both boards. The 10CL025 needs its own FPGA pin list (other ball names).

Status (2026-11-03): **schematic** generated from `tools/design.py`, drawn with wires, then edited in KiCad (the KiCad
schematic is the source of truth; `tools/check_net.py` checks it against `design.py`). **PCB: 4 layers, placed and fully
routed**: DRC 0 unconnected, 0 clearance errors, 0 schematic parity issues; only silkscreen text warnings left (reference
texts not tidied yet). The KiCad board is the source of truth (mounting holes moved by the user). Placement backup
(before routing): `archive/2026-11-03_before_routing/`.

## Board rules and checks

- Copper to board edge 0.3 mm (JLCPCB); the microSD socket J7 sits 0.25 mm inside the left edge for this.
- No vias inside small SMD pads; vias only in the large GND pads of U2 (pad 39) and U3 and in U1's tab.
- Silkscreen references 0.8 mm / 0.13 mm, each beside its part (`tools/silk.py`), connector outlines clipped at the
  board edge (DRC therefore notes "footprint differs from library" for J2-J6).
- The ESP32-WROVER-E footprint matches the datasheet land pattern (Fig. 15): pad size, pitch, pin 1 / pin 19 and
  GND pad position.
- Checks: ERC 0 / 0, `tools/check_net.py` PASS, DRC 0 errors, 0 unconnected, 0 schematic parity issues.

## Parts choice

Most resistors and small capacitors are JLCPCB **Basic** parts (no per-line fee). Extended parts: the VGA DAC, 523 / 1.05k / 2.1k /
4.22k per colour (full scale 0.70 V into 75 Ohm, steps even within about 0.02 LSB), 6p8 on the VGA lines, 68 Ohm in the AY low-pass
(23 kHz with 0.1 uF), 47.5k in the CP2102N VBUS divider, ESP32-WROVER-E, CP2102N, CH9350L, LDL1117S33R (kept over the Basic
AMS1117 for its lower dropout and better PSRR), USBLC6-2SC6, PTS810 buttons, and the connectors. USB-A J8 / J9:
SOFNG USB-302-T (C112456), as in JLCPCB's final BOM of the boards built. Older states of the board and its order files are in `archive/` (the ordered set: `archive/2026-11-03_as_ordered/`).

## JLCPCB order files (`jlcpcb/`, made by `python3 tools/jlc_export.py` in WSL)

Gerbers for 4 layers (F.Cu, In1.Cu GND, In2.Cu +3V3, B.Cu) + drill, BOM and CPL with LCSC numbers checked 2026-11-03
(identity checked on lcsc.com / jlcpcb.com; stock shows in JLCPCB's BOM check). Order: 4 layers, 1.6 mm, default
stack-up; option "via in pad, epoxy filled + capped" for the vias in the ESP32 / CP2102N centre pads. Check part
rotations in JLCPCB's placement preview (custom footprints U2, J2; U3 is rotated 180 deg). J1 and the holes are not
in the BOM / CPL.

## PCB layers and routing

| Layer | Use |
|---|---|
| F.Cu | signals + fan-out of the plane nets (no copper under the ESP32 body except its pads, see rule areas) |
| In1.Cu | **GND plane** (power layer) |
| In2.Cu | **+3V3 plane** (power layer) |
| B.Cu | signals |

- Net classes (`.kicad_pro`): signals 0.2 mm / 0.15 mm clearance, +3V3 0.3 mm, +5V and VBUS_C 0.4 mm, vias 0.6 / 0.3 mm;
  board minimum track 0.1 mm (short neck-downs at the 0.5 mm pitch CP2102N / CH9350L pins; JLCPCB minimum 0.09 mm).
- Every SMD pad on GND / +3V3 has its own via to its plane (`tools/route.py fan`); the ESP32's pad 39 has 4 GND vias
  (in the hole of the top-layer rule area); U3's centre pad connects to GND through pin 2's track and its own vias.
- USB-C corner (`tools/usbc.py`, by hand): D+ pads joined left of the pads, D- pads joined right of them under the
  connector (track only), VBUS pad pairs through vias to a B.Cu joiner and a via under U5 to its pin 5, CC1 through a
  tented via under the connector, J5's GND pins straight to the shield pads.
- CP2102N (U3) rotated 180 deg (user) so D+ / D- face the ESD part; D- crosses D+ through a B.Cu hop (`tools/dmfix.py`).
- The rest: FreeRouting 2.5.0 (plane nets ignored), driven by `tools/route.py` (prep / fan / free / import / unlock).

## PCB placement

Revision 1's outline (84.1 x 83.4 mm) and J1 position. Connectors on the edges:

| Edge | Top to bottom / left to right |
|---|---|
| Top | DB9 joystick 1 (J4), DB9 joystick 2 (J6), audio jack J3 (opening up); the corner beyond it is antenna clearance |
| Left | USB 2 J9 (5 V for a VGA2HDMI dongle) beside VGA J2, then VGA J2, microSD J7 |
| Right | ESP32-WROVER-E U2 with the antenna end 1 mm inside the edge (nothing sticks out; keep-out in the footprint), USB-C J5, USB 1 J8 (keyboard) |
| Bottom | J1 host connector (as revision 1) |

Groups: joystick pull-ups under their DB9s; VGA DAC resistors and 6p8 caps beside J2; microSD pull-ups beside J7;
audio filter left of the ESP32; ESP32 decoupling and EN RC above its pins 2 / 3, left of the antenna; CP2102N, ESD, CC resistors and
the auto-reset transistors between the ESP32 and USB-C; EN / BOOT buttons left of them; LDO in the middle; CH9350L
with the ESD part and bulk caps beside J8. Mounting holes H1-H4 inside the board (the corners hold connectors or the antenna clearance).
Rule area "ESP32 antenna clearance" (all 4 copper layers: no tracks, vias, pads, pour or parts): x 127.2 to the right edge, y 76.0-119.0 = the antenna, 15 mm of edge beside it on the side away from the feed point (Espressif "Keepout Zone for ESP32 Module's Antenna (Antenna feed point on the right)"; the feed side faces USB-C) and the strip down to USB-C.
Rule area "ESP32 body: top layer clear" (F.Cu only: no tracks, vias or pour; pads allowed) between the module's pad rows up to the antenna, with a hole around pad 39 (GND) for its vias: nothing but the module's own pads touches its underside; B.Cu under the module is for the GND fill (user's choice after a XIAO board failed on a GND fill).
The ESP32 footprint has no via pads: GND vias under its centre pad are added when routing.

Built by `tools/mk_pcb.py build` (KiCad python) from the netlist (`kicad-cli sch export netlist --format kicadxml -o
netlist.xml`) and `tools/placement.py`. Once the board is edited in KiCad, the KiCad file is the source of truth: do
not rebuild over it.

## What changes against revision 1

| Revision 1 | Revision 2 |
|---|---|
| ESP32 DevKit on two 1x15 sockets | **ESP32-WROVER-E-N16R8** module (U2, JLCPCB C529589: 16 MB flash, 8 MB PSRAM for large folder lists); the DevKit's GPIOs except the control UART (IO16 / IO17 drive the PSRAM): RX2 on IO27, TX2 on IO21; antenna at a board edge |
| (console = the DevKit's USB) | **CP2102N** (U3) on **USB-C** (J5), DTR/RTS auto-reset (Q1, Q2), EN / BOOT buttons |
| keyboard module on J5 (4-pin header) | **CH9350L** (U4) + right-angle **USB-A** J8 for the keyboard at the board edge near the CH9350L; a second right-angle USB-A J9 beside the VGA socket carries **5 V only** (power for a VGA2HDMI dongle) |
| 5 V from the core board (J1 63/64) | **5 V from USB-C** on this board, straight to +5V (no diode), which also feeds the core board via J1 63/64. Power the system from USB-C **or** the core board's DC jack, never both (no back-feed protection) |
| K7803 switching module | **LDL1117S33R** LDO (U1, 1.2 A, SOT-223) |
| THT audio capacitors | SMD (same circuit) |

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
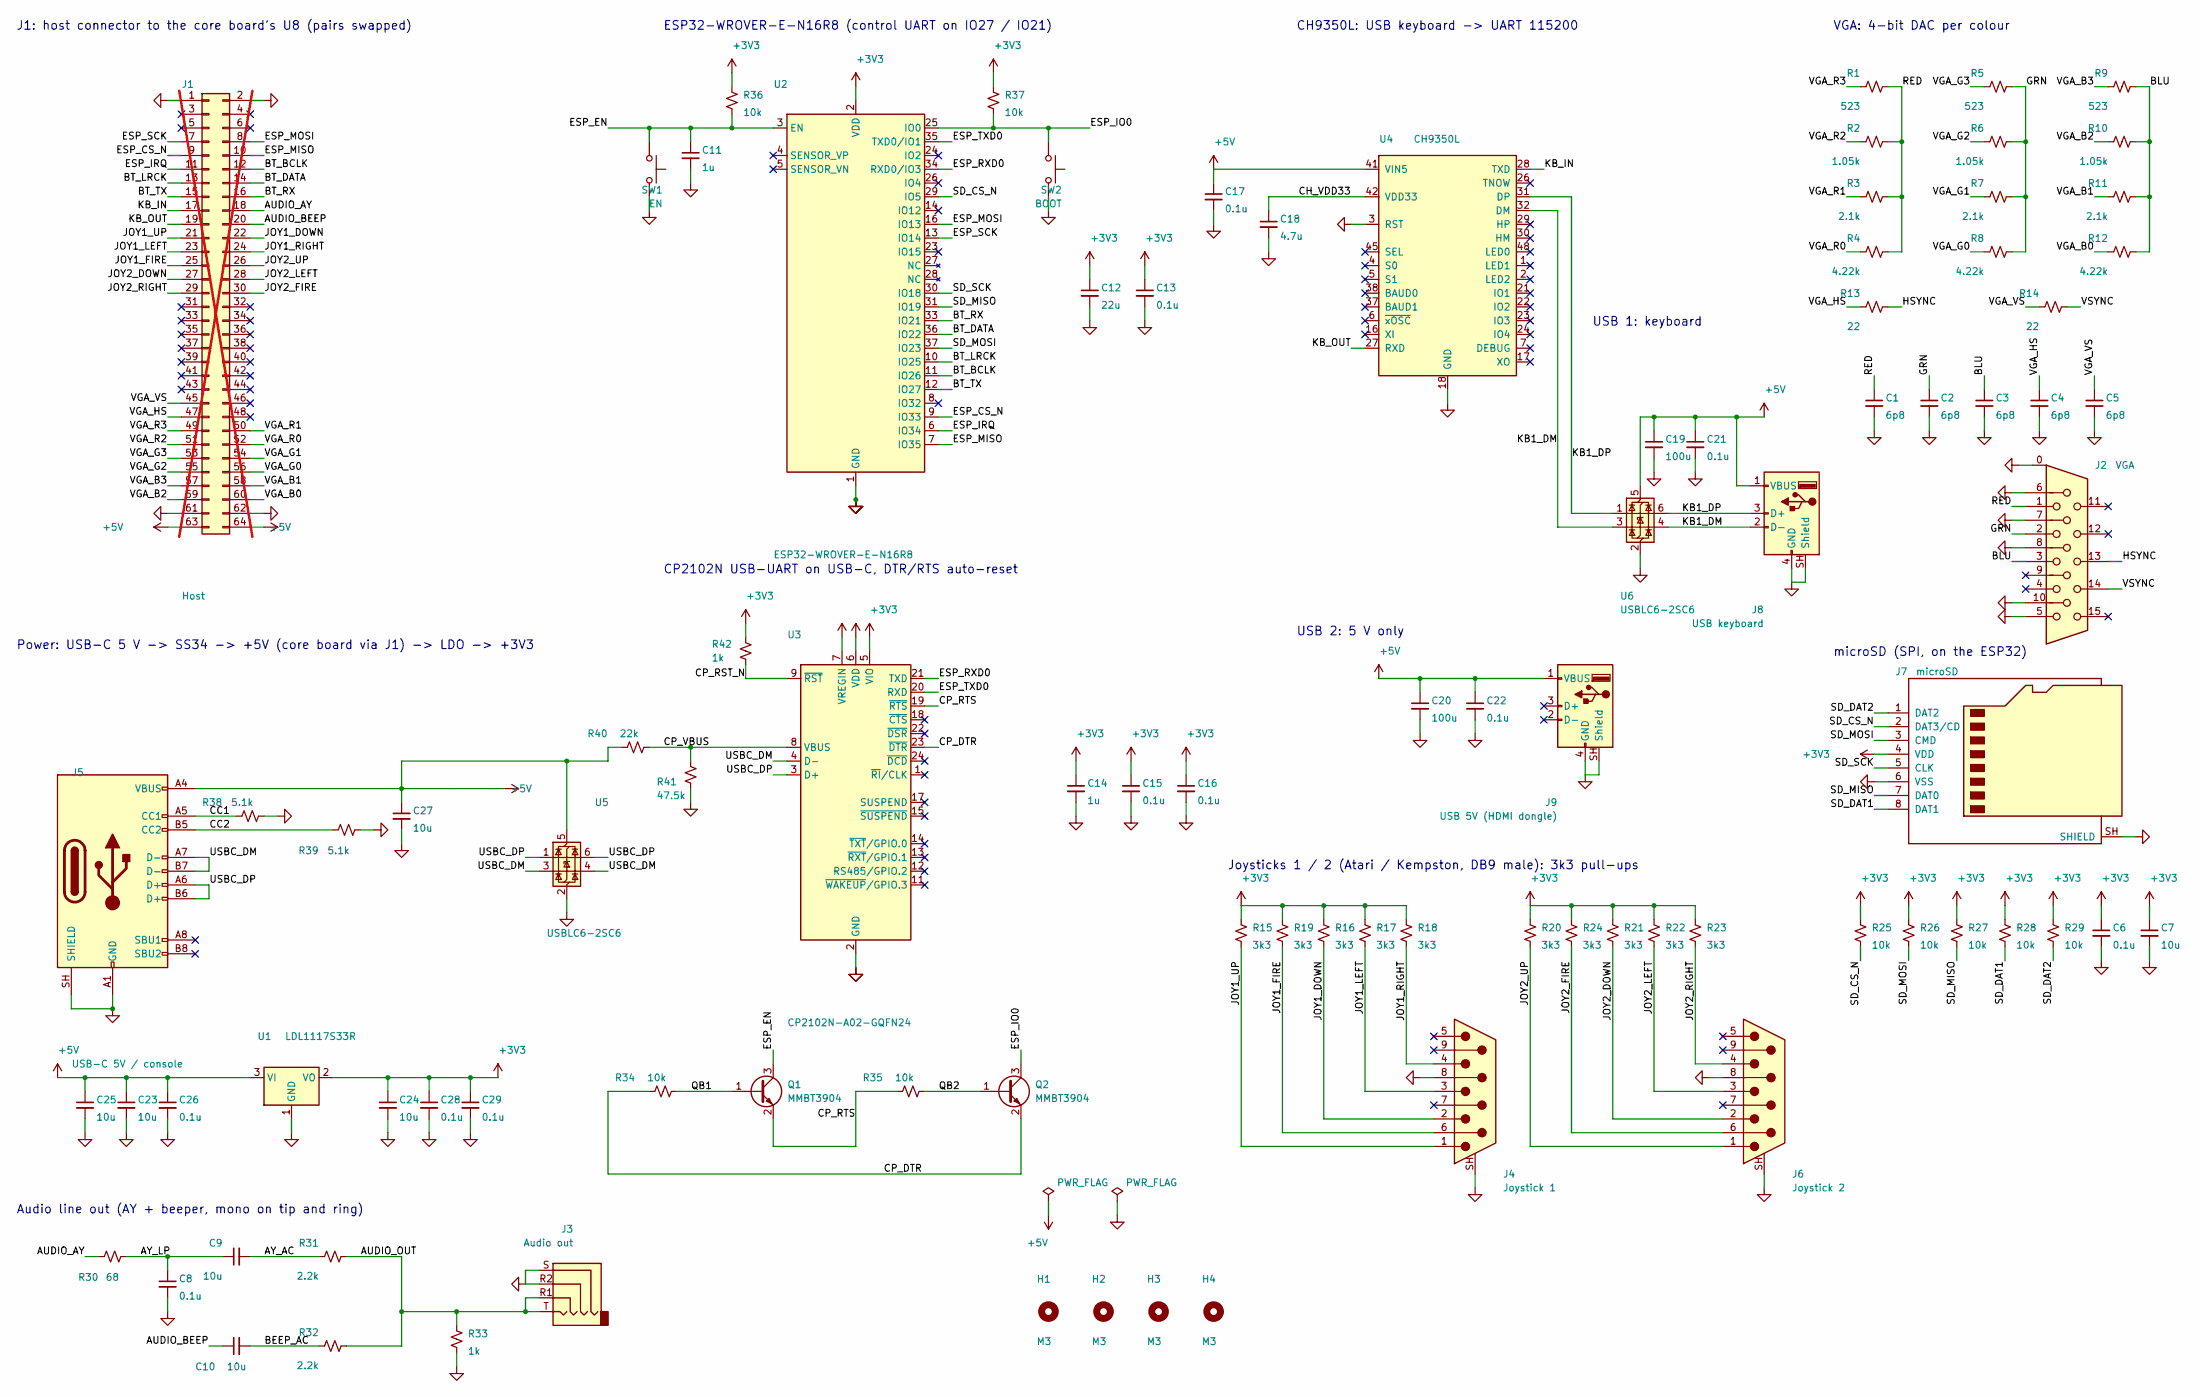
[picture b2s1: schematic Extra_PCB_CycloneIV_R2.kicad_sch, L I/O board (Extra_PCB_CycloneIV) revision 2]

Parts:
C1, C2, C3, C4, C5: 6p8; C_0603_1608Metric
C6, C8, C13, C15, C16, C17, C21, C22, C26, C28, C29: 0.1u; C_0603_1608Metric
C7, C9, C10, C23, C24, C25, C27: 10u; C_0805_2012Metric
C11, C14: 1u; C_0603_1608Metric
C12: 22u; C_0805_2012Metric
C18: 4.7u; C_0603_1608Metric
C19, C20: 100u; C_1206_3216Metric
H1, H2, H3, H4: M3; MountingHole_3.2mm_M3
J1: Host; PinHeader_2x32_P2.54mm_Vertical_RowsSwapped; not fitted
J2: VGA; DSUB-15-HD_Socket_Horizontal_P2.29x2.54mm_CONNFLY_DS1038; MPN DS1038-15FBNSiA74-0CC
J3: Audio out; Jack_3.5mm_KoreanHropartsElec_PJ-320D-4A_Horizontal; MPN PJ-320D-4A
J4: Joystick 1; DSUB-9_Pins_Horizontal_P2.77x2.84mm_EdgePinOffset7.70mm_Hou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; MPN DS1037-09MNAKT74-0CC
J5: USB-C 5V / console; USB_C_Receptacle_HRO_TYPE-C-31-M-12; MPN TYPE-C-31-M-12
J6: Joystick 2; DSUB-9_Pins_Horizontal_P2.77x2.84mm_EdgePinOffset7.70mm_Hou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; MPN DS1037-09MNAKT74-0CC
J7: microSD; microSD_HC_Molex_104031-0811; MPN 104031-0811
J8: USB keyboard; USB_A_Connfly_DS1095; MPN USB-302-T
J9: USB 5V (HDMI dongle); USB_A_Connfly_DS1095; MPN USB-302-T
Q1, Q2: MMBT3904; SOT-23; MPN MMBT3904
R1, R5, R9: 523; R_0603_1608Metric
R2, R6, R10: 1.05k; R_0603_1608Metric
R3, R7, R11: 2.1k; R_0603_1608Metric
R4, R8, R12: 4.22k; R_0603_1608Metric
R13, R14: 22; R_0603_1608Metric
R15, R16, R17, R18, R19, R20, R21, R22, R23, R24: 3k3; R_0603_1608Metric
R25, R26, R27, R28, R29, R34, R35, R36, R37: 10k; R_0603_1608Metric
R30: 68; R_0603_1608Metric
R31, R32: 2.2k; R_0603_1608Metric
R33, R42: 1k; R_0603_1608Metric
R38, R39: 5.1k; R_0603_1608Metric
R40: 22k; R_0603_1608Metric
R41: 47.5k; R_0603_1608Metric
SW1: EN; SW_SPST_PTS810; MPN PTS810SJM250SMTRLFS
SW2: BOOT; SW_SPST_PTS810; MPN PTS810SJM250SMTRLFS
U1: LDL1117S33R; SOT-223-3_TabPin2; MPN LDL1117S33R
U2: ESP32-WROVER-E-N16R8; ESP32-WROVER-E; MPN ESP32-WROVER-E-N16R8
U3: CP2102N-A02-GQFN24; QFN-24-1EP_4x4mm_P0.5mm_EP2.6x2.6mm; MPN CP2102N-A02-GQFN24R
U4: CH9350L; LQFP-48_7x7mm_P0.5mm; MPN CH9350L
U5, U6: USBLC6-2SC6; SOT-23-6; MPN USBLC6-2SC6

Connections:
+3V3: C6.1, C7.1, C12.1, C13.1, C14.1, C15.1, C16.1, C24.1, C28.1, C29.1, J7.4 (VDD), R15.1, R16.1, R17.1, R18.1, R19.1, R20.1, R21.1, R22.1, R23.1, R24.1, R25.1, R26.1, R27.1, R28.1, R29.1, R36.1, R37.1, R42.1, U1.2 (VO), U2.2 (VDD), U3.5 (VIO), U3.6 (VDD), U3.7 (VREGIN)
+5V: C17.1, C19.1, C20.1, C21.1, C22.1, C23.1, C25.1, C26.1, C27.1, J1.63, J1.64, J5.A4 (VBUS), J5.A9 (VBUS), J5.B4 (VBUS), J5.B9 (VBUS), J8.1 (VBUS), J9.1 (VBUS), R40.1, U1.3 (VI), U4.41 (VIN5), U5.5 (VBUS), U6.5 (VBUS)
/AUDIO_AY: J1.18, R30.1
/AUDIO_BEEP: C10.1, J1.20
/AUDIO_OUT: J3.R1, J3.T, R31.2, R32.2, R33.1
/AY_AC: C9.2, R31.1
/AY_LP: C8.1, C9.1, R30.2
/BEEP_AC: C10.2, R32.1
/BLU: C3.1, J2.3, R9.2, R10.2, R11.2, R12.2
/BT_BCLK: J1.12, U2.11 (IO26)
/BT_DATA: J1.14, U2.36 (IO22)
/BT_LRCK: J1.13, U2.10 (IO25)
/BT_RX: J1.16, U2.33 (IO21)
/BT_TX: J1.15, U2.12 (IO27)
/CC1: J5.A5 (CC1), R38.1
/CC2: J5.B5 (CC2), R39.1
/CH_VDD33: C18.1, U4.42 (VDD33)
/CP_DTR: Q2.2 (E), R34.1, U3.23 (~DTR)
/CP_RST_N: R42.2, U3.9 (~RST)
/CP_RTS: Q1.2 (E), R35.1, U3.19 (~RTS)
/CP_VBUS: R40.2, R41.1, U3.8 (VBUS)
/ESP_CS_N: J1.9, U2.9 (IO33)
/ESP_EN: C11.1, Q1.3 (C), R36.2, SW1.1, U2.3 (EN)
/ESP_IO0: Q2.3 (C), R37.2, SW2.1, U2.25 (IO0)
/ESP_IRQ: J1.11, U2.6 (IO34)
/ESP_MISO: J1.10, U2.7 (IO35)
/ESP_MOSI: J1.8, U2.16 (IO13)
/ESP_RXD0: U2.34 (RXD0/IO3), U3.21 (TXD)
/ESP_SCK: J1.7, U2.13 (IO14)
/ESP_TXD0: U2.35 (TXD0/IO1), U3.20 (RXD)
/GRN: C2.1, J2.2, R5.2, R6.2, R7.2, R8.2
/HSYNC: J2.13, R13.2
/JOY1_DOWN: J1.22, J4.2, R16.2
/JOY1_FIRE: J1.25, J4.6, R19.2
/JOY1_LEFT: J1.23, J4.3, R17.2
/JOY1_RIGHT: J1.24, J4.4, R18.2
/JOY1_UP: J1.21, J4.1, R15.2
/JOY2_DOWN: J1.27, J6.2, R21.2
/JOY2_FIRE: J1.30, J6.6, R24.2
/JOY2_LEFT: J1.28, J6.3, R22.2
/JOY2_RIGHT: J1.29, J6.4, R23.2
/JOY2_UP: J1.26, J6.1, R20.2
/KB1_DM: J8.2 (D-), U4.32 (DM), U6.3 (I/O2), U6.4 (I/O2)
/KB1_DP: J8.3 (D+), U4.31 (DP), U6.1 (I/O1), U6.6 (I/O1)
/KB_IN: J1.17, U4.28 (TXD)
/KB_OUT: J1.19, U4.27 (RXD)
/QB1: Q1.1 (B), R34.2
/QB2: Q2.1 (B), R35.2
/RED: C1.1, J2.1, R1.2, R2.2, R3.2, R4.2
/SD_CS_N: J7.2 (DAT3/CD), R25.2, U2.29 (IO5)
/SD_DAT1: J7.8 (DAT1), R28.2
/SD_DAT2: J7.1 (DAT2), R29.2
/SD_MISO: J7.7 (DAT0), R27.2, U2.31 (IO19)
/SD_MOSI: J7.3 (CMD), R26.2, U2.37 (IO23)
/SD_SCK: J7.5 (CLK), U2.30 (IO18)
/USBC_DM: J5.A7 (D-), J5.B7 (D-), U3.4 (D-), U5.3 (I/O2), U5.4 (I/O2)
/USBC_DP: J5.A6 (D+), J5.B6 (D+), U3.3 (D+), U5.1 (I/O1), U5.6 (I/O1)
/VGA_B0: J1.60, R12.1
/VGA_B1: J1.58, R11.1
/VGA_B2: J1.59, R10.1
/VGA_B3: J1.57, R9.1
/VGA_G0: J1.56, R8.1
/VGA_G1: J1.54, R7.1
/VGA_G2: J1.55, R6.1
/VGA_G3: J1.53, R5.1
/VGA_HS: C4.1, J1.47, R13.1
/VGA_R0: J1.52, R4.1
/VGA_R1: J1.50, R3.1
/VGA_R2: J1.51, R2.1
/VGA_R3: J1.49, R1.1
/VGA_VS: C5.1, J1.45, R14.1
/VSYNC: J2.14, R14.2
GND: C1.2, C2.2, C3.2, C4.2, C5.2, C6.2, C7.2, C8.2, C11.2, C12.2, C13.2, C14.2, C15.2, C16.2, C17.2, C18.2, C19.2, C20.2, C21.2, C22.2, C23.2, C24.2, C25.2, C26.2, C27.2, C28.2, C29.2, J1.1, J1.2, J1.61, J1.62, J2.0 (GND), J2.5, J2.6, J2.7, J2.8, J2.10, J3.R2, J3.S, J4.8, J4.SH (PAD), J5.A1 (GND), J5.A12 (GND), J5.B1 (GND), J5.B12 (GND), J5.SH (SHIELD), J6.8, J6.SH (PAD), J7.6 (VSS), J7.SH (SHIELD), J8.4 (GND), J8.SH (Shield), J9.4 (GND), J9.SH (Shield), R33.2, R38.2, R39.2, R41.2, SW1.2, SW2.2, U1.1 (GND), U2.1 (GND), U2.15 (GND), U2.38 (GND), U2.39 (GND), U3.2 (GND), U3.25 (GND), U4.3 (RST), U4.18 (GND), U5.2 (GND), U6.2 (GND)

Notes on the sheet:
Audio line out (AY + beeper, mono on tip and ring)
Joysticks 1 / 2 (Atari / Kempston, DB9 male): 3k3 pull-ups
microSD (SPI, on the ESP32)
VGA: 4-bit DAC per colour
Power: USB-C 5 V -> SS34 -> +5V (core board via J1) -> LDO -> +3V3
USB 2: 5 V only
ESP32-WROVER-E-N16R8 (control UART on IO27 / IO21)
J1: host connector to the core board's U8 (pairs swapped)
CP2102N USB-UART on USB-C, DTR/RTS auto-reset
CH9350L: USB keyboard -> UART 115200
USB 1: keyboard

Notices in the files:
README.md:
prints adapted from the KiCad libraries (D-Sub 15 HD, pin headers); revision 2's ESP32-WROVER-E footprint is own work from Espressif's land pattern | CC-BY-SA 4.0 with the KiCad library exception (designs made with them, the board files and Gerbers included, are not bound by it); the rest of the boa
Because of the GPL-3 parts, the LSpectrum, L64, LMega and LNext bitstreams (and `L.jic`, and their machine files) are GPL-3 works. Details, the
